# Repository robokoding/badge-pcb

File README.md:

nametag
=======

LED dot matrix name tag

bill of materials
=================
**ebay:**
* 1 x [Tilt switch](http://www.ebay.com/itm/251612655766)<br>
* 1 x [MCP73831T](http://www.ebay.com/itm/251610085563)<br>
* 2 x [SPDT slide switch](http://www.ebay.com/itm/201095465543)<br>
* 1 x [3.7V 130mAh Li-Po](http://www.ebay.com/itm/130617227476)<br>
* 1 x [3.3V 8MHz Pro Mini](http://www.ebay.com/itm/231368307663) <br>
* 1 x [HT1632C LED Driver](http://www.ebay.com/itm/251685195429) <br>
* 1 x [Micro Mini JST Connector](http://www.ebay.com/itm/271631717682161344644655)<br>

**local electronics store:**
* 1 x 2kΩ resistor
* 8 x 33Ω resistor
* 1 x 330Ω resistor
* 1 x red SMD LED
* 1 x 3V zener diode
* 3 x 4.7uF ceramic capacitor
* 1 x 4.7uF electrolytic capacitor
* some female and male pin headers

**tips:**
* instread the Pro Mini [Pro Micro](http://www.ebay.com/itm/140972980117) or [Pro Micro BLE](http://www.ebay.com/itm/251696382555) can be used

assembly instruction
====================
happy soldering ^_^

datasheets
==========
[HT1632C](http://www.adafruit.com/datasheets/ht1632cv120.pdf) <br>
[MCP73831T](https://www.sparkfun.com/datasheets/Prototyping/Batteries/MCP73831T.pdf) <br>

credits ^_^
===========
[Arduino wiring](https://learn.adafruit.com/16x24-led-matrix/wiring) <br>
[Sparkfun FIO board](https://www.sparkfun.com/products/11520) <br>
[Adafruit EAGLE library](https://github.com/adafruit/Adafruit-Eagle-Library/blob/master/adafruit.lbr) <br>
[HT1632C Arduino library](https://github.com/adafruit/HT1632) <br>
[HT1632C reference board](http://2.bp.blogspot.com/-Hhg82y6URPg/UglrFuE2HcI/AAAAAAAAALw/jM5RPzM6XEs/s1600/back.jpg) <br>
[Sparkfun EAGLE libraries](https://github.com/sparkfun/SparkFun-Eagle-Libraries) <br>
[Titlt switch istructables](http://www.instructables.com/id/Tilt-Sensor-Tutorial/step5/Reading-switch-state-with-a-microcontroller/) <br>
[hosentraeger EAGLE library](https://github.com/hosentraeger/LED-Matrix-HT1632/blob/master/ht1632.lbr) <br>
[Sparkfun USB Li-Po charger](https://www.sparkfun.com/products/10217) <br>
[Jaycon Systems USB Li-Po charger](http://www.jayconsystems.com/micro-usb-lipo-charger-mcp73831.html) <br>
[Adafuit Trinket / Gemma Space Invader Pendant](https://learn.adafruit.com/trinket-slash-gemma-space-invader-pendant/wirin) <br>

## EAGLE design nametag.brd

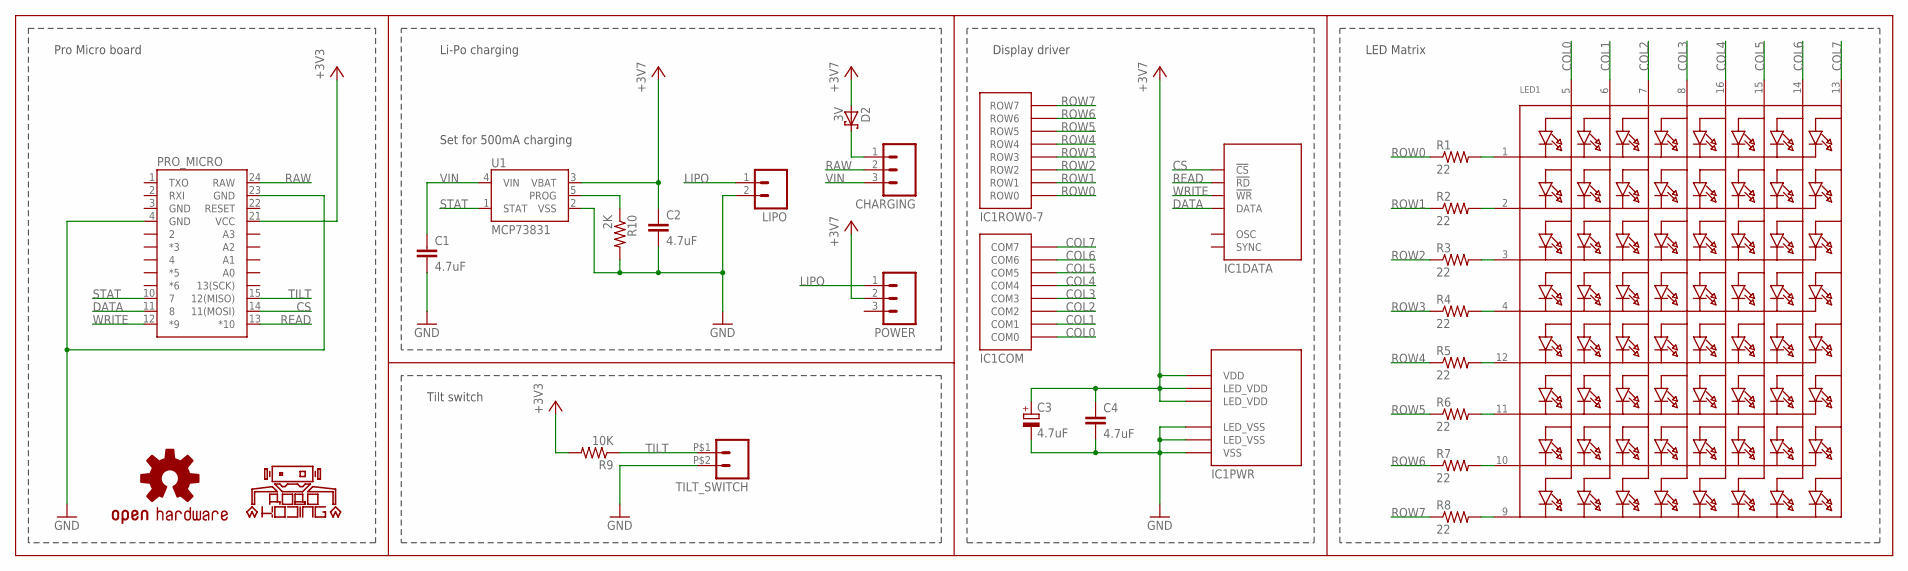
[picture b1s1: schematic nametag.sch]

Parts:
C1, C2, C4: 4.7uF; 0402-CAP
C3: 4.7uF; PANASONIC_B
CHARGING: M03PTH; 1X03
D2: 3V; SOD323_ST
IC1: HT1632; QFP52
LED1: SEGMENT_8X8_ROWCATHODE; SEGMENT_BL-M07C881UR
LIPO: M02JST-PTH-VERT; JST-2-PTH-VERT
LOGO1: OSHW-LOGOS; OSHW-LOGO-S
LOGO2: ROBOKODING-LOGOS; ROBOKODING-LOGO-S
POWER: M03PTH; 1X03
PRO_MICRO: ARDUINO_PRO_MICRO
R1, R2, R3, R4, R5, R6, R7, R8: 22; 0402-RES
R9: 10K; 0402-RES
R10: 2K; 0402-RES
TILT_SWITCH: M02PTH2; 1X02_BIG
U1: MCP73831; SOT23-5

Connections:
+3V3: C2.1, C3.+, C4.1, D2.A, IC1.P$7 (LED_VDD), IC1.P$21 (VDD), IC1.P$38 (LED_VDD), POWER.2, U1.3 (VBAT)
COL0: IC1.P$22 (COM0), LED1.5 (A1)
COL1: IC1.P$23 (COM1), LED1.6 (A2)
COL2: IC1.P$24 (COM2), LED1.7 (A3)
COL3: IC1.P$26 (COM3), LED1.8 (A4)
COL4: IC1.P$27 (COM4), LED1.16 (A5)
COL5: IC1.P$28 (COM5), LED1.15 (A6)
COL6: IC1.P$29 (COM6), LED1.14 (A7)
COL7: IC1.P$30 (COM7), LED1.13 (A8)
CS: IC1.P$19 (!CS), PRO_MICRO.14 (11(MOSI))
DATA: IC1.P$16 (DATA), PRO_MICRO.11 (8)
GND: C1.2, C2.2, C3.-, C4.2, IC1.P$14 (VSS), IC1.P$25 (LED_VSS), IC1.P$36 (LED_VSS), LIPO.2, PRO_MICRO.4 (GND), PRO_MICRO.23 (GND), R10.2, TILT_SWITCH.P$2 (2), U1.2 (VSS)
LIPO: LIPO.1, POWER.1
unnamed: LED1.1 (K1), R1.2
unnamed: LED1.2 (K2), R2.2
unnamed: CHARGING.1, D2.C
unnamed: LED1.3 (K3), R3.2
unnamed: LED1.4 (K4), R4.2
unnamed: LED1.12 (K5), R5.2
unnamed: LED1.11 (K6), R6.2
unnamed: LED1.10 (K7), R7.2
unnamed: LED1.9 (K8), R8.2
PROG: R10.1, U1.5 (PROG)
RAW: CHARGING.2, PRO_MICRO.24 (RAW)
READ: IC1.P$18 (!RD), PRO_MICRO.13 (*10)
ROW0: IC1.P$13 (ROW0), R1.1
ROW1: IC1.P$12 (ROW1), R2.1
ROW2: IC1.P$11 (ROW2), R3.1
ROW3: IC1.P$10 (ROW3), R4.1
ROW4: IC1.P$9 (ROW4), R5.1
ROW5: IC1.P$8 (ROW5), R6.1
ROW6: IC1.P$6 (ROW6), R7.1
ROW7: IC1.P$5 (ROW7), R8.1
STAT: PRO_MICRO.10 (7), U1.1 (STAT)
TILT: PRO_MICRO.15 (12(MISO)), R9.1, TILT_SWITCH.P$1 (1)
VCC: PRO_MICRO.21 (VCC), R9.2
VIN: C1.1, CHARGING.3, U1.4 (VIN)
WRITE: IC1.P$17 (!WR), PRO_MICRO.12 (*9)

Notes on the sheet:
Li-Po charging
Display driver
Pro Micro board
LED Matrix
Set for 500mA charging
Tilt switch

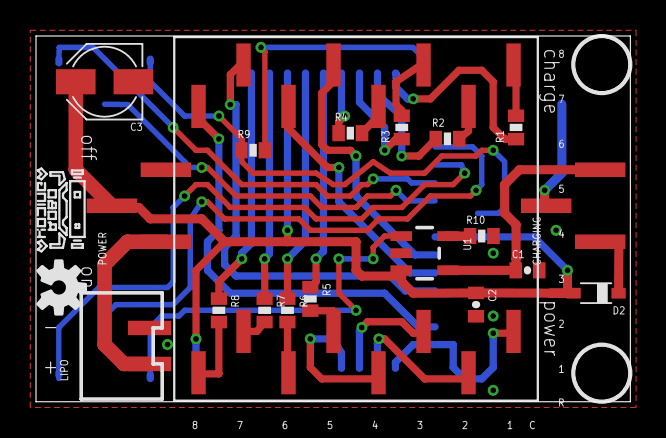
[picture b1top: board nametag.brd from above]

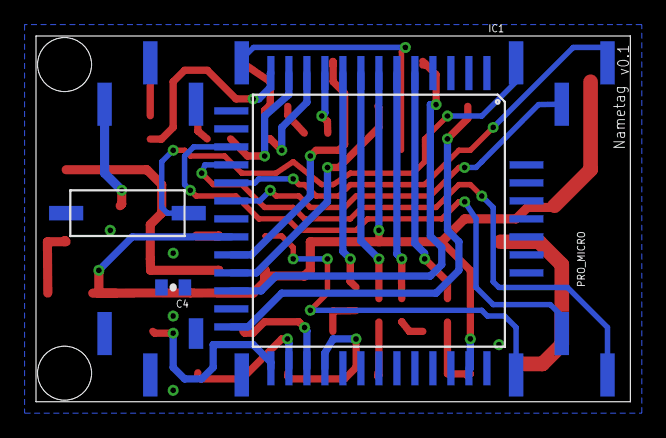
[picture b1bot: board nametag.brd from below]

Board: 2 copper layers, 33.0 x 20.3 mm, 27 parts (6 on the bottom side), 38 nets.

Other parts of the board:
U$1, U$2: 3,0

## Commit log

2014-11-20 added EAGLE schematics and board
2014-11-22 separated battery and microcontroller VCC
2014-11-22 updated routes
2014-11-22 added logos
2014-11-22 updated logos
2015-01-02 updated nametag schematic and board
2015-01-10 Update LICENSE

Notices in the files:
parts and their libraries:
SparkFun-Boards: Licensing: Creative Commons ShareAlike 4.0 International - https://creativecommons.org/licenses/by-sa/4.0
